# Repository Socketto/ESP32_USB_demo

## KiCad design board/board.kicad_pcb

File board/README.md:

# ESP32 USB demo - KiCad board

ESP32-WROOM-32E-N4 demonstration board with one USB-C port, a WCH CH340C
application USB-to-UART bridge, external UART0 programming headers, a 3.3 V
regulator, and a TFT SPI connector.

> **Work in progress, not production-ready.** The PCB has no tracks, vias,
> or copper zones. Exported Gerber, BOM, and CPL files are placement snapshots,
> not a finished board suitable for ordering. Complete routing and resolve
> manufacturing issues before fabrication.
>
> **Connect either the external programmer or Serial1 USB, never both.**
> During programming, the programmer supplies regulated 3.3 V through J4.
> Disconnect the programmer completely before connecting Serial1 USB.
> UART signals must use 3.3 V logic, never 5 V or RS-232 voltages.

## Overview

*Component placement, not a routed board.*

| Block | Components and function |
| --- | --- |
| Microcontroller | U1, ESP32-WROOM-32E-N4, Wi-Fi/Bluetooth and 4 MB flash |
| Application USB-C | Serial1 and U2 CH340C, connected to ESP32 UART2; R12/R13 are the USB-C CC pull-downs |
| External programming | J4 exposes UART0, EN/reset, GPIO0/BOOT, ground and the common +3V3 rail |
| Manual boot/reset | Use J4 pin 6 (GPIO0), pin 5 (EN) and pin 2 (GND); no separate BOOT/RESET headers |
| Boot/reset bias | R5/R6, 10 kOhm EN/GPIO0 pull-ups; C6, 1 uF EN-to-ground reset timing |
| Power | U3 USB regulator output and J4 pin 1 share +3V3 directly; no source selector or reverse-current isolation |
| Display | J1, 8-pin TFT SPI header |
| Indicators and inputs | D1 RGB LED, IN1 push button, TH1 10 kOhm B3950 NTC |
| Configuration | DA1 solder jumper |

The second programming USB connector FLASHER1, its CH340C U4, automatic-reset
transistors Q1/Q2, and associated R18/R19/R20/R21/C7/C8/C10 have been removed.
Serial1 remains the **application UART2 interface**, not the ESP32 ROM
programming interface. UART2 requires matching firmware configuration.
There is no on-board DTR/RTS auto-reset circuit in this revision.

The independent [`board_cp2102n` project](../board_cp2102n/README.md) has not
been changed: it retains two CP2102N bridges, two USB-C connectors, and
automatic programming. The two projects therefore no longer differ only
in bridge choice; account for these functional differences when comparing
JLCPCB quotations.

## External programming

J4 uses a six-pin, through-hole, 2.54 mm vertical header. The table gives
**KiCad pad numbers**, not an assumed left-to-right connector view; pad 1
is square. Board labels TX/RX refer to the ESP32, not the adapter.

| J4 pin | Signal | External adapter connection |
| --- | --- | --- |
| 1 | +3V3, common board rail | Programmer's regulated 3.3 V output; Serial1 USB must be disconnected |
| 2 | GND | Adapter GND |
| 3 | TXD0_ESP, GPIO1/U0TXD | Adapter RX input |
| 4 | RXD0_ESP, GPIO3/U0RXD | Adapter TX output |
| 5 | ESP_EN, reset | Briefly connect to pin 2 (GND), then release to reset |
| 6 | ESP_BOOT, GPIO0 | Connect to pin 2 (GND) during reset to enter download mode |

J4 pin 1, U3's output and the board loads are directly connected to the same
`+3V3` rail. No power-selection jumper is required. This arrangement assumes
physically exclusive connections: unplug Serial1 USB for programming, then
disconnect the programmer completely before using Serial1 USB.

BOOT and RESET are operated directly through J4; separate BOOT1/RST1 headers
are not fitted. Use temporary leads to GND as described below; do not keep EN
grounded during flashing or normal operation.
R5/R6 remain necessary even without auto-reset: they establish the normal
high levels of EN and GPIO0. C6 remains connected between EN and GND.

### Manual flashing sequence

1. Make sure Serial1 USB is disconnected and all power is off.
2. Connect a regulated **3.3 V supply** to J4 pin 1 and GND to pin 2.
   The supply must support the ESP32's current peaks and other board loads;
   many USB-to-UART adapter 3.3 V outputs are not rated for this load.
   Connect a 3.3 V logic USB-to-UART adapter's GND, RX and TX as shown above.
   Use a common ground. Do not connect Serial1 USB while the programmer is connected.
3. Connect J4 pin 6 to pin 2 (GND) to pull GPIO0 low.
4. Briefly connect J4 pin 5 to GND, then release it while keeping GPIO0 low. The ESP32
   enters its ROM serial download mode when EN rises.
5. Select the **external adapter's** serial port in `esptool` or the IDE,
   not Serial1/U2. Use manual boot/reset handling rather than expecting an
   on-board DTR/RTS reset circuit. Disable RTS/CTS hardware flow control.
6. After flashing, release GPIO0 and disconnect the programmer and any external
   supply completely. Connect Serial1 USB to run the application.

For normal USB operation, leave J4 GPIO0 and EN released.
EN and GPIO0 are exposed
for a suitable external programming circuit, but **do not directly wire
adapter DTR/RTS to them** without a correctly designed ESP32 reset circuit.
The adapter's driver depends on its bridge; the on-board U2 uses the WCH
CH340/CH341 driver.

### TFT SPI pinout

| J1 pin | Signal |
| --- | --- |
| 1 | +3V3 |
| 2 | GND |
| 3 | SPI_CS |
| 4 | SPI_RESET |
| 5 | SPI_DC |
| 6 | SPI_SDA, SPI data |
| 7 | SPI_SCK |
| 8 | +3V3 |

Check that the display accepts 3.3 V power and logic. `SPI_SDA` is the
SPI data net name here, not an I2C connection.

## CH340C, USB and power

U2 uses CH340C, **C84681**, in
`Package_SO:SOIC-16_3.9x9.9mm_P1.27mm`. It is not pin-compatible with
CP2102N. Its application UART operates at ESP32-safe 3.3 V logic levels.

| U2 pin | Connection |
| --- | --- |
| 16, VCC and 4, V3 | Both tied to regulated +3V3 |
| 1, GND and 15, R232 | Ground; normal non-inverted TTL UART mode |
| 5, UD+ and 6, UD- | Serial1 D+ and D-, respectively |
| 2, TXD and 3, RXD | Application UART2, with TX/RX crossed to the ESP32 |
| 7-14 | Unused clock/OUT/modem/control pins |

This is the manufacturer's **external 3.3 V supply mode**. Do not apply
5 V to VCC while V3 remains tied to it. C9 supplies local 100 nF bypass
decoupling; route its ground return and the bridge supply connections short.
CH340C has an internal clock and power-on reset, and no VBUS-sense input.
The former CP2102N reset pull-ups R7/R22 and sensing divider R14/R15
are absent. See the [WCH CH340 datasheet](https://www.lcdwiki.com/res/PublicFile/CH340C_en.pdf).

Serial1 D+ (A6/B6) and D- (A7/B7) connect directly to U2 pins 5 and 6.
No external series USB resistors or USB pull-up are required. There is no
external USB data-line ESD array, reducing protection against connector
electrostatic discharge. Route the differential pair appropriately.
With only one board USB connector, the former dual-VBUS power-sharing
restriction no longer applies to this project. Respect USB host current
limits and the ESP32/display power budget.

U3 remains **TI TLV1117LV33DCYR**, with the pin-compatible 1117 symbol and
SOT-223 footprint. Its maximum operating input is 5.5 V. Keep this
ceramic-stable TI regulator rather than substituting a generic AMS1117
without checking stability. C5 is nonpolar 22 uF / 25 V X5R ceramic 1206;
allow for DC-bias/temperature derating and retain at least the regulator's
required effective capacitance. During external programming, U3's OUT remains
connected to +3V3 while its USB input is floating. Its internal body diode
can charge the input capacitors and raise the disconnected VBUS rail below
the external 3.3 V supply. There is no reverse-current isolation; verify the
startup transient on assembled hardware, especially if adding VBUS loads.
TI documents that reverse current is not internally limited; see the
[TLV1117LV datasheet, section 7.3.1](https://www.ti.com/lit/ds/symlink/tlv1117lv.pdf).

## Schematic and files

*Open the image to zoom in. KiCad sources are authoritative.*

| Path | Contents |
| --- | --- |
| `board.kicad_pro` | KiCad project to open |
| `board.kicad_sch` | Schematic |
| `board.kicad_pcb` | Unrouted PCB placement |
| `esp32_usb.kicad_sym`, `sym-lib-table` | Project CH340C symbol for external 3.3 V supply mode |
| `images/` | README schematic and PCB snapshots |
| `jlcpcb/project.db` | Plugin assignments, export exclusions and local corrections |
| `jlcpcb/gerber/` | Generated Gerber and drill files |
| `jlcpcb/production_files/` | Generated Gerber archive, BOM and CPL |

Sources use **KiCad 10**. Install standard symbol and footprint libraries;
the schematic also embeds a connector symbol originating from
`PCM_JLCPCB-Extended`. Serial1 uses
`Connector_USB:USB_C_Receptacle_HCTL_HC-TYPE-C-16P-01A`.
The local `ESP32_USB:CH340C_3V3` symbol represents V3 as a power input,
matching external 3.3 V operation and avoiding a false ERC power-output
conflict. Keep both local-library files with the project.

Generated `jlcpcb/gerber/` and `jlcpcb/production_files/` directories are
ignored by Git. Regenerate from current sources before uploading. Keep
the plugin database and documentation images under version control.
Editor history, lock files, autosaves and `*.kicad_prl` are also ignored.

## Required KiCad plugin for JLCPCB

Use **[bouni/kicad-jlcpcb-tools](https://github.com/bouni/kicad-jlcpcb-tools)**,
shown in KiCad as **JLCPCB Tools**. It assigns LCSC/JLCPCB parts and generates
Gerber, Excellon, BOM and CPL files. *Fabrication Toolkit* is a different
plugin and may apply different rotation corrections.

### Installation

1. Open KiCad's **Plugin and Content Manager**, then its repository manager.
2. Add the author's repository:

   ```text
   https://raw.githubusercontent.com/Bouni/bouni-kicad-repository/main/repository.json
   ```

3. Install **KiCad JLCPCB tools**, then restart the PCB Editor or refresh plugins.
4. Open **Tools > External Plugins > JLCPCB Tools**.

See the [official installation documentation](https://github.com/bouni/kicad-jlcpcb-tools#installation-)
for current requirements and interface changes.

### Main catalog assignments

| Reference | Manufacturer part | JLCPCB | Notes |
| --- | --- | --- | --- |
| U1 | ESP32-WROOM-32E-N4 | [C701341](https://jlcpcb.com/partdetail/C701341) | ESP32 module |
| U2 | CH340C | [C84681](https://jlcpcb.com/partdetail/C84681) | WCH SOP-16, internal clock |
| U3 | TLV1117LV33DCYR | [C15578](https://jlcpcb.com/partdetail/C15578) | Ceramic-stable TI regulator |
| C3 | 1206B475K500NT | [C29823](https://jlcpcb.com/partdetail/C29823) | Basic, 4.7 uF / 50 V X7R, 1206 |
| C4, C6 | CL31B105KBHNNNE | [C1848](https://jlcpcb.com/partdetail/C1848) | Basic, 1 uF / 50 V X7R, 1206 |
| C5 | CL31A226KAHNNNE | [C12891](https://jlcpcb.com/partdetail/C12891) | Basic, nonpolar 22 uF / 25 V X5R, 1206 |
| R12, R13 | 0603WAF5101T5E | [C23186](https://jlcpcb.com/partdetail/C23186) | Basic, 5.1 kOhm 1%, USB CC pull-downs |
| Serial1 | HC-TYPE-C-16P-01A | [C2894897](https://jlcpcb.com/partdetail/C2894897) | HCTL USB-C, matching footprint |
| J1, J4 | Standard 2.54 mm pin headers | Unassigned | Source and assemble manually |

J4 remains in the schematic and PCB but is **excluded from both BOM and CPL**
because it is manually assembled and has no assigned LCSC part. This prevents
JLCPCB reporting a BOM designator missing from the CPL. Source manual headers
separately, or deliberately select compatible catalog parts and a supported
through-hole assembly service before changing exclusions.

Existing cost-reduced Basic passive assignments are retained. The previous
dual-CH340C component estimate of USD 32.75 for five boards is **historical,
not the current BOM total**. This revision removes eleven components per
board and adds three manually assembled headers. Five remaining CH340C
devices use a different catalog quantity tier than ten devices: in the
previous snapshot, USD 0.546 instead of USD 0.456 each.
Removing one of two identical bridges does not remove its feeder code.
Compare freshly uploaded BOMs for actual component, assembly, feeder and
possible QFN X-ray charges; header/shunt sourcing, shipping and taxes are
additional. See [JLCPCB assembly pricing](https://jlcpcb.com/help/article/pcb-assembly-price).

### Export and upload

1. Save sources, update PCB from schematic as needed, and finish routing.
2. Run ERC and DRC, including schematic parity, and resolve errors.
3. Open JLCPCB Tools; check assignments, footprints, BOM/CPL exclusions and
   local corrections. Schematic fields alone may not update stored assignments.
4. Generate all outputs from the same PCB revision and plugin.
5. Upload `GERBER-board.zip`, `BOM-board.csv` and `CPL-board.csv` from
   `jlcpcb/production_files/`.
6. Inspect centering, assembly side, IC pin 1, lead alignment and LED polarity
   in JLCPCB's preview. Verify that removed programming components are absent.

Do not mix versions or upload old `production` exports. Negative CPL Y
coordinates are not inherently incorrect; they must match the Gerber origin.

### D1 RGB LED placement correction

The [ROHM SMLVN6RGB1U1 datasheet, Figure 1](https://fscdn.rohm.com/en/products/databook/datasheet/opto/led/chip_multi/smlvn6rgb1u1-e.pdf)
places the anode index at the upper-left corner in top view: pins 1/2/3 are
the blue/red/green anodes on the left, and pins 6/5/4 are their cathodes on
the right. The KiCad footprint and schematic use this mapping correctly.

The supplied JLCPCB preview with the original 0-degree CPL placed the
orientation marker at the opposite, lower-right corner. The local exact-value
rule `^SMLVN6RGB1U1$` therefore applies **180 degrees with zero X/Y offsets**.
D1 remains at 0 degrees in KiCad and exports at 180 degrees in the CPL.
This is an assembly-export correction, not a change to the physical footprint
or electrical connections. Re-upload the regenerated CPL and confirm the
model's anode index aligns with the upper-left pin-1 mark before ordering.
The corrected JLCPCB preview has not yet been confirmed.

### U2 placement correction

U2 retains the existing `^SOIC-` **270-degree package correction**. At its
0-degree PCB orientation, the CPL exports 270 degrees. This changes export
orientation, not the footprint's physical placement. Confirm CH340C pin 1
and lead alignment in the JLCPCB preview; the old CP2102N preview cannot
validate the current SOP-16 device.

The historical exact-value CP2102N and MMBT3904 rules remain in
`project.db`, but no current component matches them. Q1/Q2 are removed.
Keep the database: in this plugin version, local rules **replace**, rather
than extend, the global correction table. Global rules were copied locally
to preserve other packages' behavior. Recheck after updates or part changes.

## Open issues before fabrication

- **Routing is missing:** no tracks, vias or zones; unconnected pads remain.
- **Serial1:** existing HCTL hole-to-copper clearances are approximately
  0.185 mm against the project's 0.25 mm minimum. Correct geometry or confirm
  manufacturing requirements; do not lower constraints just to hide errors.
- **U1:** footprint 0.2 mm holes are below the project's 0.3 mm drill minimum;
  verify footprint/process requirements.
- **Silkscreen and assembly:** existing overlaps remain; confirm U2
  orientation in the assembly preview.
- **Schematic libraries:** existing embedded-symbol/library warnings and
  unused ESP32 GPIO findings remain to be resolved or explicitly reviewed.

The images and local outputs reflect the external-programming revision.
Regenerate them after further source changes.

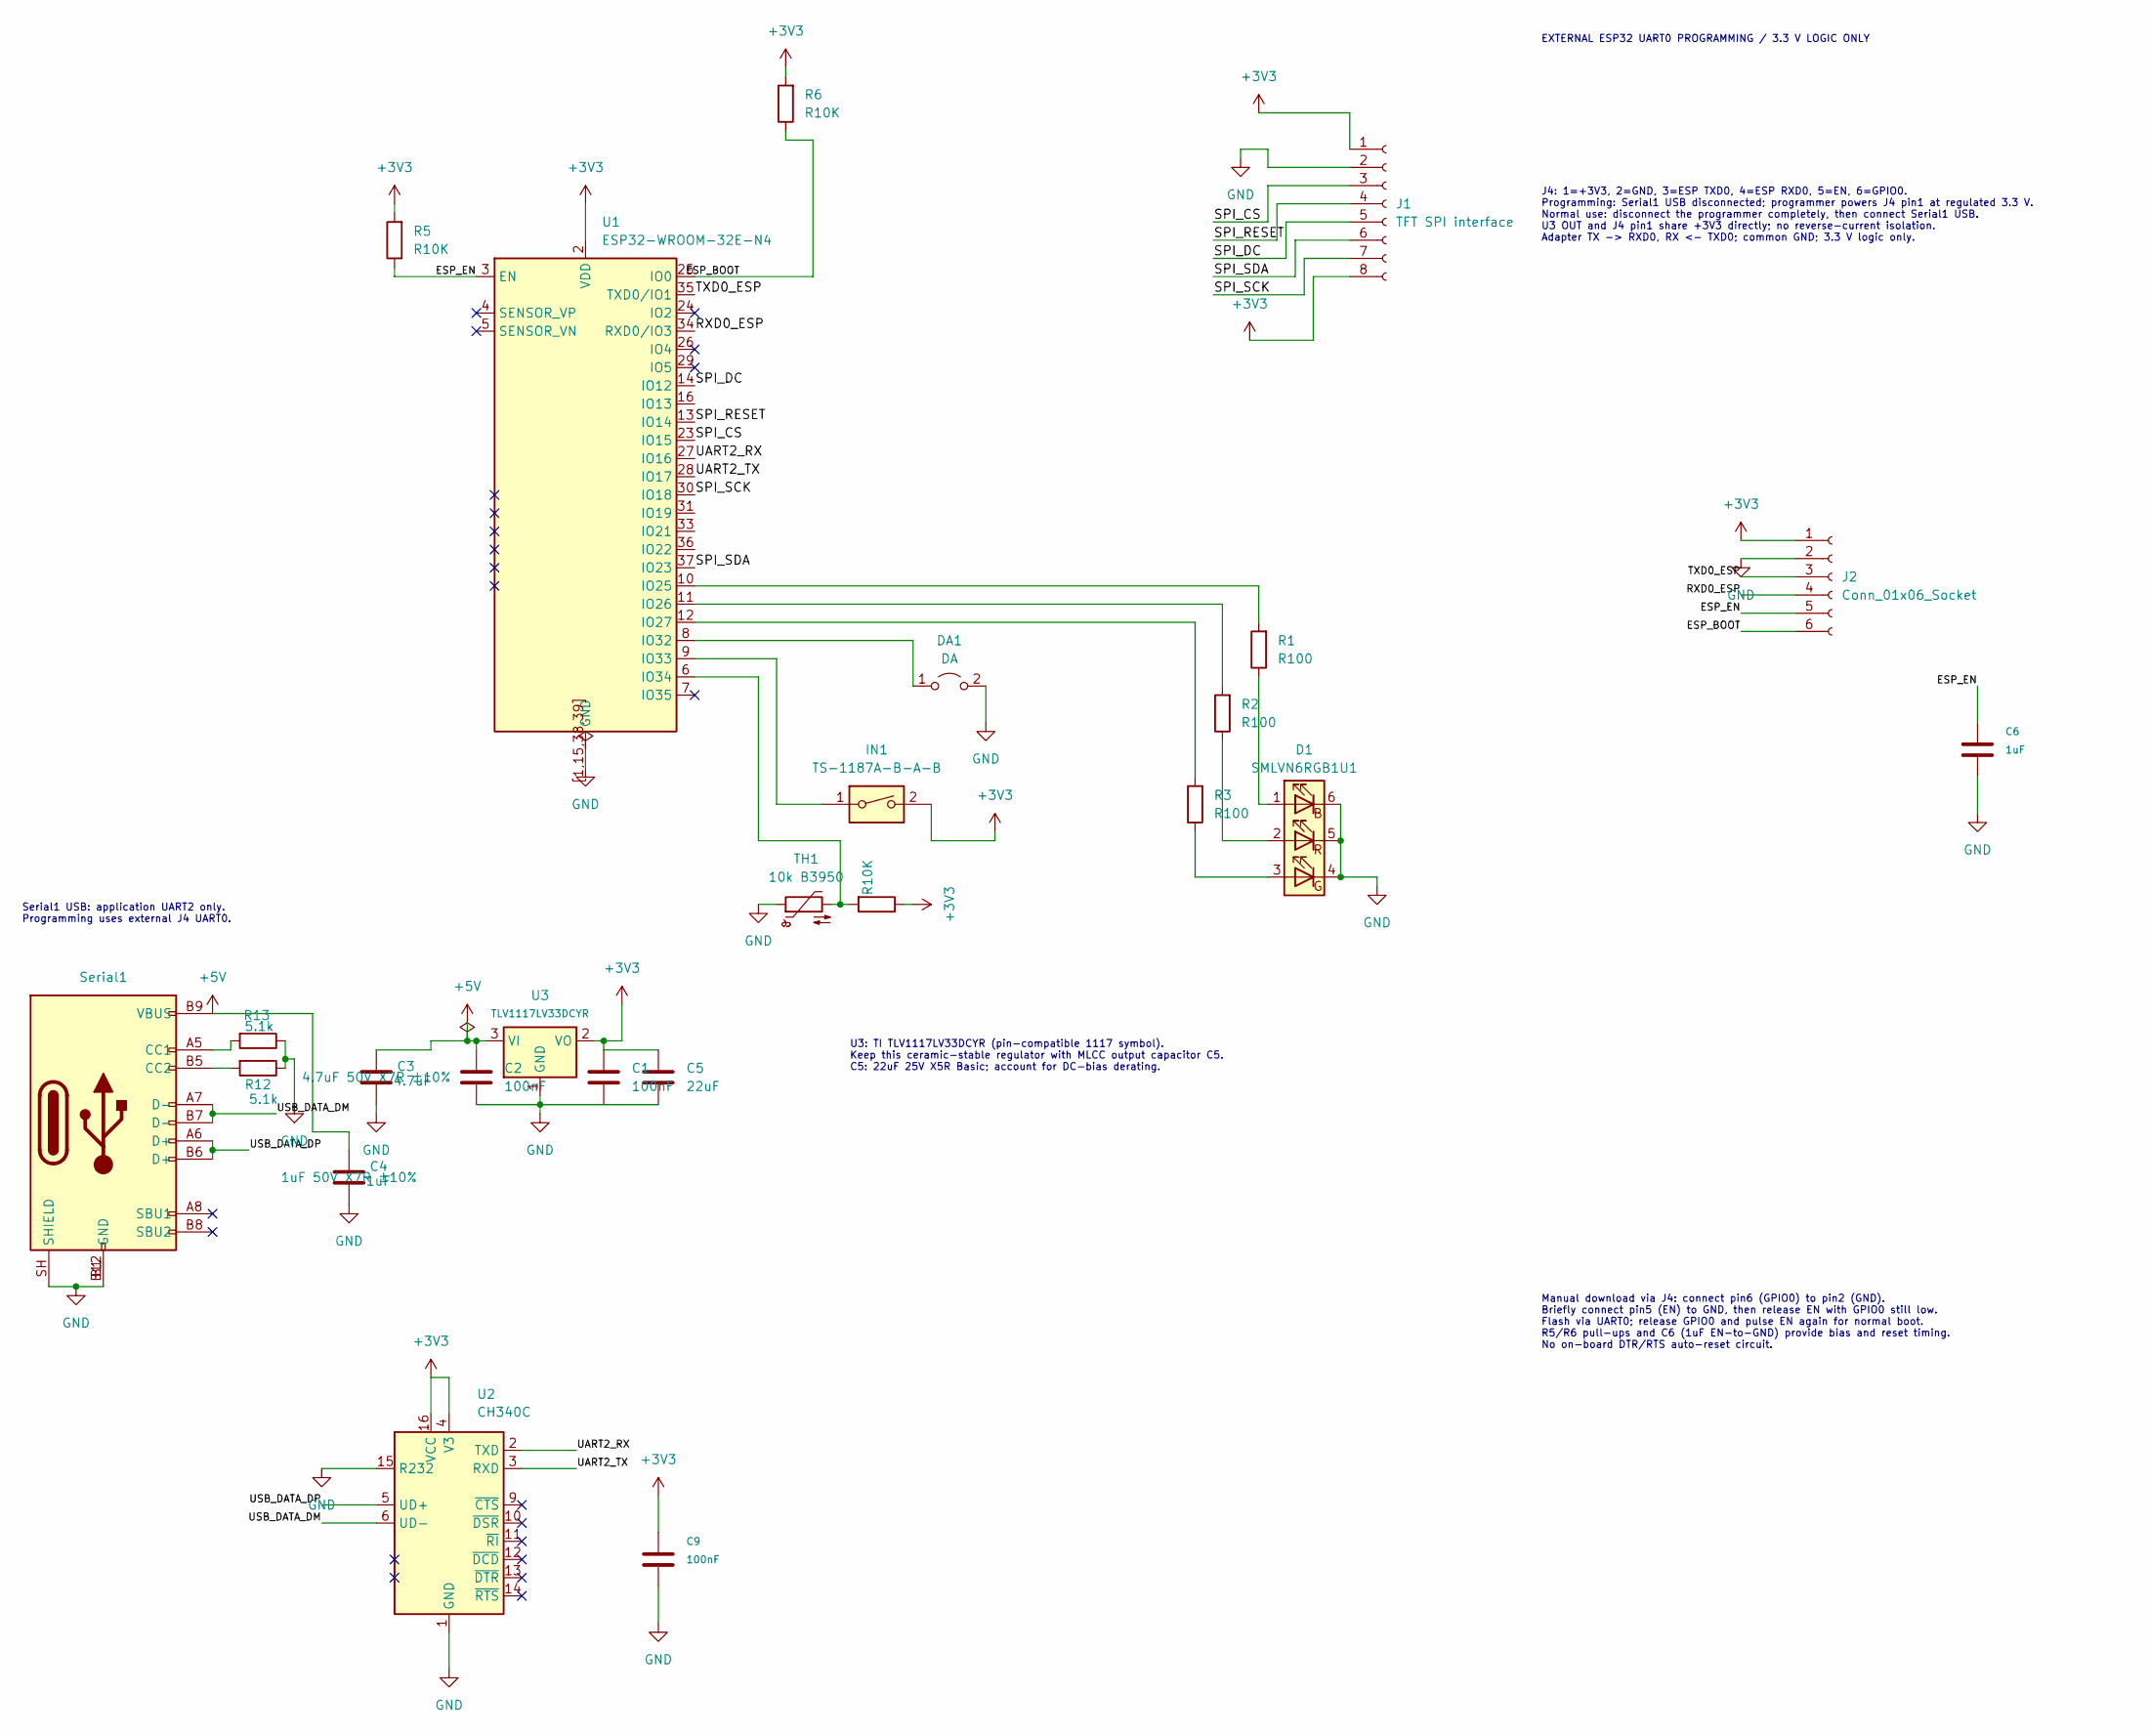
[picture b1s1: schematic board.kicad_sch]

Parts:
C1, C2, C9: 100nF; C_1206_3216Metric; MPN CL31B104KBCNNNC; LCSC C24497
C3: 4.7uF; C_1206_3216Metric; MPN 1206B475K500NT; LCSC C29823
C4, C6: 1uF; C_1206_3216Metric; MPN CL31B105KBHNNNE; LCSC C1848
C5: 22uF; C_1206_3216Metric; MPN CL31A226KAHNNNE; LCSC C12891
D1: SMLVN6RGB1U1; LED_ROHM_SMLVN6; MPN SMLVN6RGB1U1; LCSC C2909770
DA1: DA; PinHeader_1x02_P2.54mm_Vertical
IN1: TS-1187A-B-A-B; SW_Push_1P1T_XKB_TS-1187A; MPN TS-1187A-B-A-B; LCSC C318884
J1: TFT SPI interface; PinHeader_1x08_P2.54mm_Vertical
J2: Conn_01x06_Socket; PinHeader_1x06_P2.54mm_Vertical
R1, R2, R3: R100; R_1206_3216Metric; MPN 1206W4F1000T5E; LCSC C17901
R5, R6, R8: R10K; R_1206_3216Metric; MPN 1206W4F1002T5E; LCSC C17902
R12, R13: 5.1k; R_0603_1608Metric; MPN 0603WAF5101T5E; LCSC C23186
Serial1: HC-TYPE-C-16P-01A; USB_C_Receptacle_HCTL_HC-TYPE-C-16P-01A; MPN HC-TYPE-C-16P-01A; LCSC C2894897
TH1: 10k B3950; R_0805_2012Metric; MPN CMFB103J3950HANT; LCSC C338623
U1: ESP32-WROOM-32E-N4; ESP32-WROOM-32E; MPN ESP32-WROOM-32E-N4; LCSC C701341
U2: CH340C; SOIC-16_3.9x9.9mm_P1.27mm; MPN CH340C; LCSC C84681
U3: TLV1117LV33DCYR; SOT-223-3_TabPin2; MPN TLV1117LV33DCYR; LCSC C15578

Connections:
+3V3: C1.1, C5.1, C9.1, IN1.2, J1.1, J1.8, J2.1, R5.2, R6.2, R8.1, U1.2 (VDD), U2.4 (V3), U2.16 (VCC), U3.2 (VO)
+5V: C2.1, C3.1, C4.1, Serial1.A4 (VBUS), Serial1.A9 (VBUS), Serial1.B4 (VBUS), Serial1.B9 (VBUS), U3.3 (VI)
/ESP_BOOT: J2.6, R6.1, U1.25 (IO0)
/ESP_EN: C6.1, J2.5, R5.1, U1.3 (EN)
/RXD0_ESP: J2.4, U1.34 (RXD0/IO3)
/SPI_CS: J1.3, U1.23 (IO15)
/SPI_DC: J1.5, U1.14 (IO12)
/SPI_RESET: J1.4, U1.13 (IO14)
/SPI_SCK: J1.7, U1.30 (IO18)
/SPI_SDA: J1.6, U1.37 (IO23)
/TXD0_ESP: J2.3, U1.35 (TXD0/IO1)
/UART2_RX: U1.27 (IO16), U2.2 (TXD)
/UART2_TX: U1.28 (IO17), U2.3 (RXD)
/USB_DATA_DM: Serial1.A7 (D-), Serial1.B7 (D-), U2.6 (UD-)
/USB_DATA_DP: Serial1.A6 (D+), Serial1.B6 (D+), U2.5 (UD+)
GND: C1.2, C2.2, C3.2, C4.2, C5.2, C6.2, C9.2, D1.4 (GK), D1.5 (RK), D1.6 (BK), DA1.2 (B), J1.2, J2.2, R12.1, R13.1, Serial1.A1 (GND), Serial1.A12 (GND), Serial1.B1 (GND), Serial1.B12 (GND), Serial1.SH (SHIELD), TH1.1, U1.1 (GND), U1.15 (GND), U1.38 (GND), U1.39 (GND), U1.[1,15,38,39] (GND), U2.1 (GND), U2.15 (R232), U3.1 (GND)
unnamed: D1.1 (BA), R1.1
unnamed: D1.3 (GA), R3.1
unnamed: D1.2 (RA), R2.1
unnamed: DA1.1 (A), U1.8 (IO32)
unnamed: R13.2, Serial1.A5 (CC1)
unnamed: R12.2, Serial1.B5 (CC2)
unnamed: R1.2, U1.10 (IO25)
unnamed: R2.2, U1.11 (IO26)
unnamed: R3.2, U1.12 (IO27)
unnamed: IN1.1, U1.9 (IO33)
unnamed: R8.2, TH1.2, U1.6 (IO34)

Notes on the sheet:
Serial1 USB: application UART2 only. Programming uses external J4 UART0.
J4: 1=+3V3, 2=GND, 3=ESP TXD0, 4=ESP RXD0, 5=EN, 6=GPIO0. Programming: Serial1 USB disconnected; programmer powers J4 pin1 at regulated 3.3 V. Normal use: disconnect the programmer completely, then connect Serial1 USB. U3 OUT and J4 pin1 share +3V3 directly; no reverse-current isolation. Adapter TX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
EXTERNAL ESP32 UART0 PROGRAMMING / 3.3 V LOGIC ONLY
U3: TI TLV1117LV33DCYR (pin-compatible 1117 symbol). Keep this ceramic-stable regulator with MLCC output capacitor C5. C5: 22uF 25V X5R Basic; account for DC-bias derating.
Manual download via J4: connect pin6 (GPIO0) to pin2 (GND). Briefly connect pin5 (EN) to GND, then release EN with GPIO0 still low. Flash via UART0; release GPIO0 and pulse EN again for normal boot. R5/R6 pull-ups and C6 (1uF EN-to-GND) provide bias and reset timing. No on-board DTR/RTS auto-reset 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

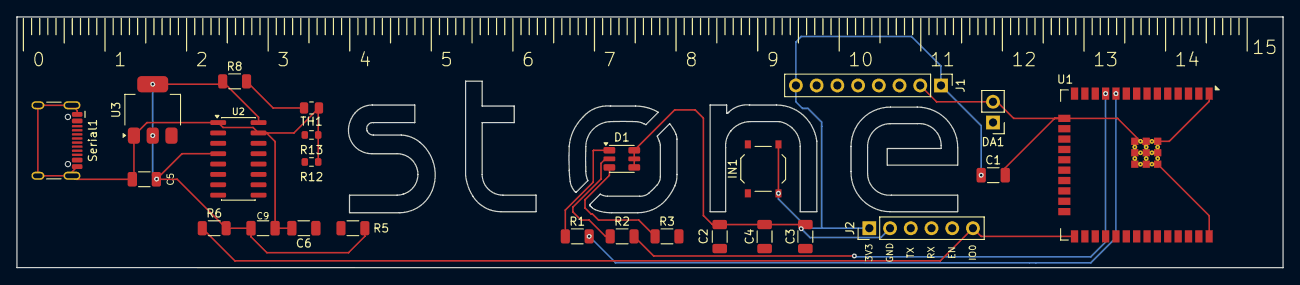
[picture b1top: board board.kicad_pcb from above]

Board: 2 copper layers, 155.2 x 30.7 mm, 25 parts (0 on the bottom side), 27 nets.
